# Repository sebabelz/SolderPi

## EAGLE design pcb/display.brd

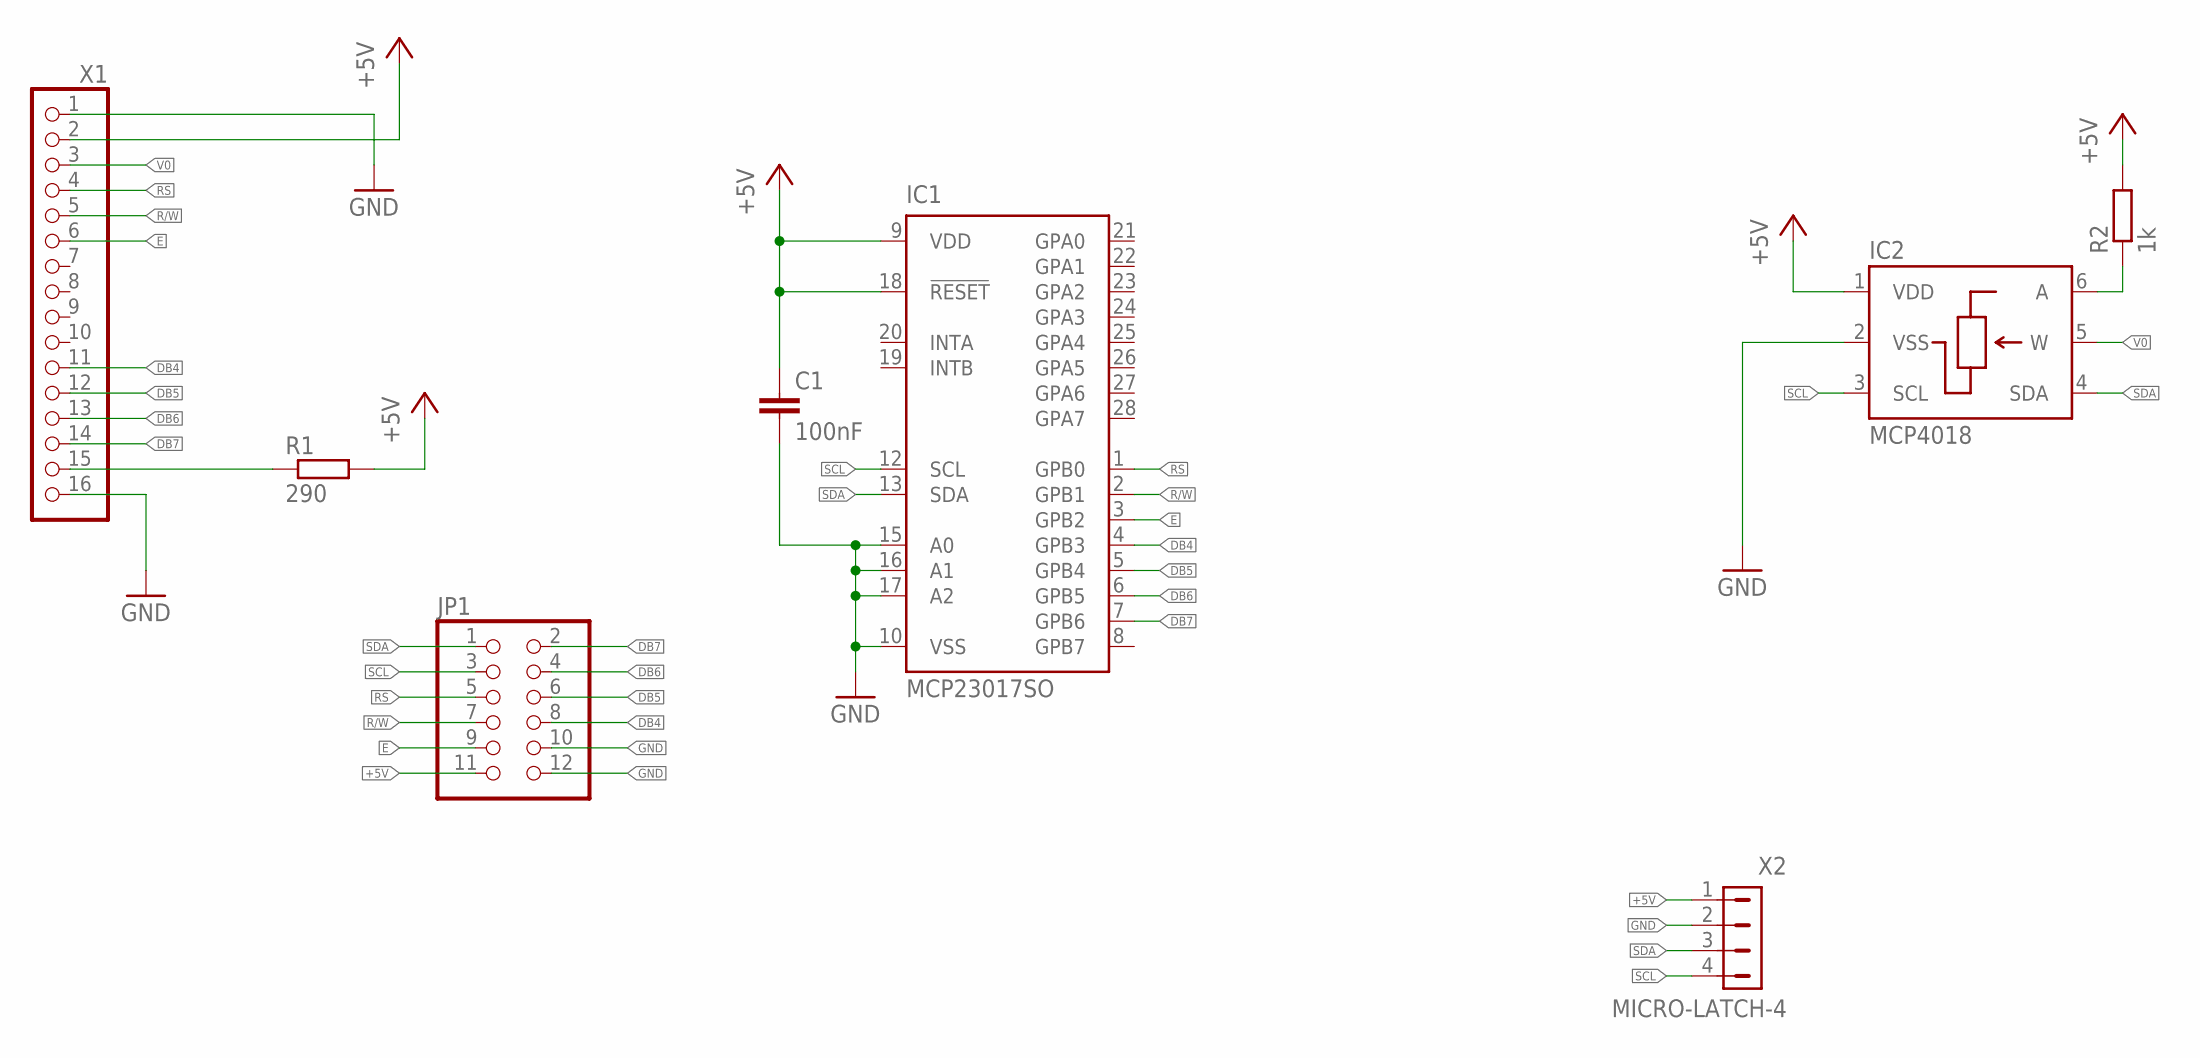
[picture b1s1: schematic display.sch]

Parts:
C1: 100nF; C0805
IC1: MCP23017SO; SO28W
IC2: MCP4018; SC70-6L
JP1: PINHD-2X6; 2X06
R1: 290; R0805
R2: 1k; R0805
X1: PINHD-1X16; 1X16
X2: MICRO-LATCH-4

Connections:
+5V: C1.1, IC1.9 (VDD), IC1.18 (!RESET), IC2.1 (VDD), JP1.11, R1.2, R2.2, X1.2, X2.1
DB4: IC1.4 (GPB3), JP1.8, X1.11
DB5: IC1.5 (GPB4), JP1.6, X1.12
DB6: IC1.6 (GPB5), JP1.4, X1.13
DB7: IC1.7 (GPB6), JP1.2, X1.14
E: IC1.3 (GPB2), JP1.9, X1.6
GND: C1.2, IC1.10 (VSS), IC1.15 (A0), IC1.16 (A1), IC1.17 (A2), IC2.2 (VSS), JP1.10, JP1.12, X1.1, X1.16, X2.2
unnamed: R1.1, X1.15
unnamed: IC2.6 (A), R2.1
R/W: IC1.2 (GPB1), JP1.7, X1.5
RS: IC1.1 (GPB0), JP1.5, X1.4
SCL: IC1.12 (SCL), IC2.3 (SCL), JP1.3, X2.4
SDA: IC1.13 (SDA), IC2.4 (SDA), JP1.1, X2.3
V0: IC2.5 (W), X1.3

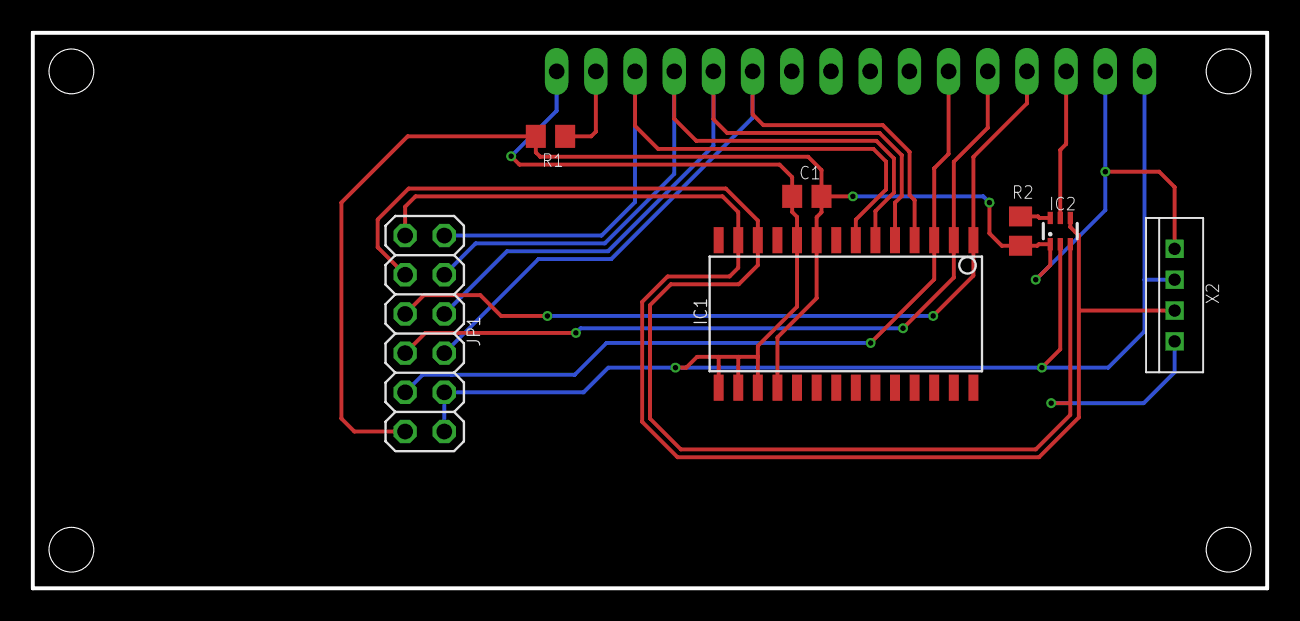
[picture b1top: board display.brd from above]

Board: 2 copper layers, 80.0 x 36.0 mm, 8 parts (1 on the bottom side), 14 nets.
